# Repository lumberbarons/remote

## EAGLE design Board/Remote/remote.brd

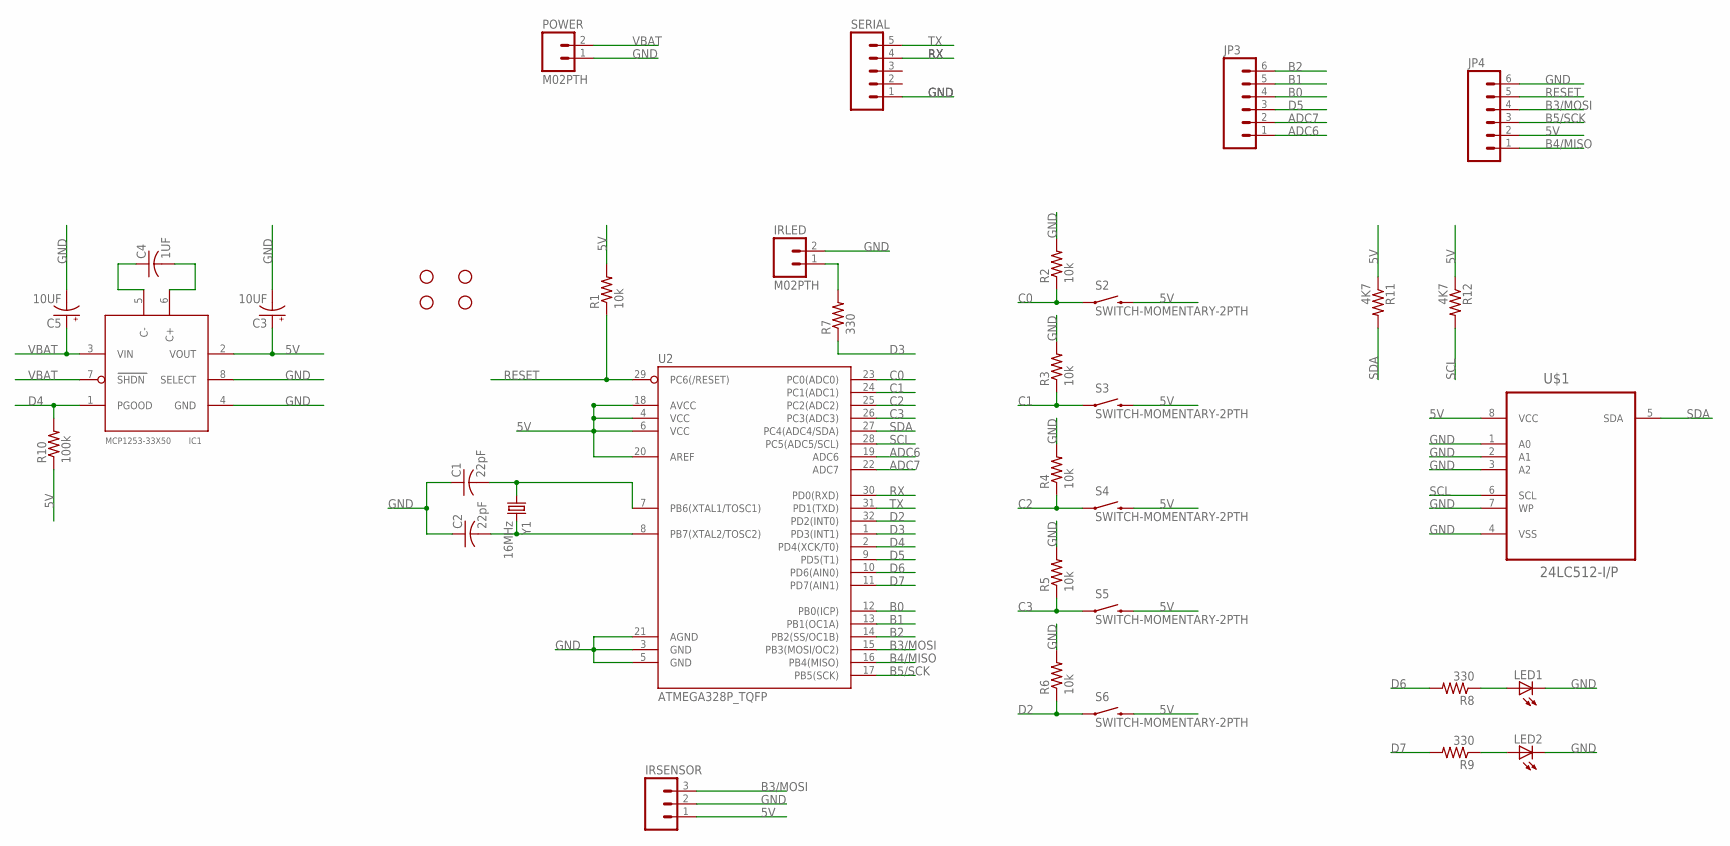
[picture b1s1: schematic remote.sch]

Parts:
C1, C2: 22pF; C0805
C3, C5: 10UF; A/3216-18W
C4: 1UF; C0805
IC1: MCP1253-33X50; MSOP8
IRLED: M02PTH; 1X02
IRSENSOR: M03PTH; 1X03
JP1, JP2, JP6, JP7: STAND-OFF
JP3, JP4: M06SIP; 1X06
LED1, LED2: LEDCHIPLED_0805; CHIPLED_0805
POWER: M02PTH; 1X02
R1, R2, R3, R4, R5, R6: 10k; R0805
R7, R8, R9: 330; R0805
R10: 100k; R0805
R11, R12: 4K7; R0805
S2, S3, S4, S5, S6: SWITCH-MOMENTARY-2PTH; TACTILE-PTH
SERIAL: M05PTH; 1X05
U2: ATMEGA328P_TQFP; TQFP32-08
U$1: 24LC512-I/P; DIP254P762X432-8
Y1: 16MHz; HC49US

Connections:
5V: C3.+, IC1.2 (VOUT), IRSENSOR.1, JP4.2, R1.2, R10.1, R11.1, R12.1, S2.3 (2), S3.3 (2), S4.3 (2), S5.3 (2), S6.3 (2), U2.4 (VCC), U2.6 (VCC), U2.18 (AVCC), U2.20 (AREF), U$1.8 (VCC)
ADC6: JP3.1, U2.19 (ADC6)
ADC7: JP3.2, U2.22 (ADC7)
B0: JP3.4, U2.12 (PB0(ICP))
B1: JP3.5, U2.13 (PB1(OC1A))
B2: JP3.6, U2.14 (PB2(SS/OC1B))
B3/MOSI: IRSENSOR.3, JP4.4, U2.15 (PB3(MOSI/OC2))
B4/MISO: JP4.1, U2.16 (PB4(MISO))
B5/SCK: JP4.3, U2.17 (PB5(SCK))
C0: R2.1, S2.1, U2.23 (PC0(ADC0))
C1: R3.1, S3.1, U2.24 (PC1(ADC1))
C2: R4.1, S4.1, U2.25 (PC2(ADC2))
C3: R5.1, S5.1, U2.26 (PC3(ADC3))
D2: R6.1, S6.1, U2.32 (PD2(INT0))
D3: R7.1, U2.1 (PD3(INT1))
D4: IC1.1 (PGOOD), R10.2, U2.2 (PD4(XCK/T0))
D5: JP3.3, U2.9 (PD5(T1))
D6: R8.2, U2.10 (PD6(AIN0))
D7: R9.2, U2.11 (PD7(AIN1))
GND: C1.1, C2.1, C3.-, C5.-, IC1.4 (GND), IC1.8 (SELECT), IRLED.2, IRSENSOR.2, JP4.6, LED1.C, LED2.C, POWER.1, R2.2, R3.2, R4.2, R5.2, R6.2, SERIAL.1, U2.3 (GND), U2.5 (GND), U2.21 (AGND), U$1.1 (A0), U$1.2 (A1), U$1.3 (A2), U$1.4 (VSS), U$1.7 (WP)
unnamed: C1.2, U2.7 (PB6(XTAL1/TOSC1)), Y1.1
unnamed: C2.2, U2.8 (PB7(XTAL2/TOSC2)), Y1.2
unnamed: IRLED.1, R7.2
unnamed: LED1.A, R8.1
unnamed: LED2.A, R9.1
unnamed: C4.1, IC1.5 (C-)
unnamed: C4.2, IC1.6 (C+)
RESET: JP4.5, R1.1, U2.29 (PC6(/RESET))
RX: SERIAL.4, U2.30 (PD0(RXD))
SCL: R12.2, U2.28 (PC5(ADC5/SCL)), U$1.6 (SCL)
SDA: R11.2, U2.27 (PC4(ADC4/SDA)), U$1.5 (SDA)
TX: SERIAL.5, U2.31 (PD1(TXD))
VBAT: C5.+, IC1.3 (VIN), IC1.7 (SHDN), POWER.2

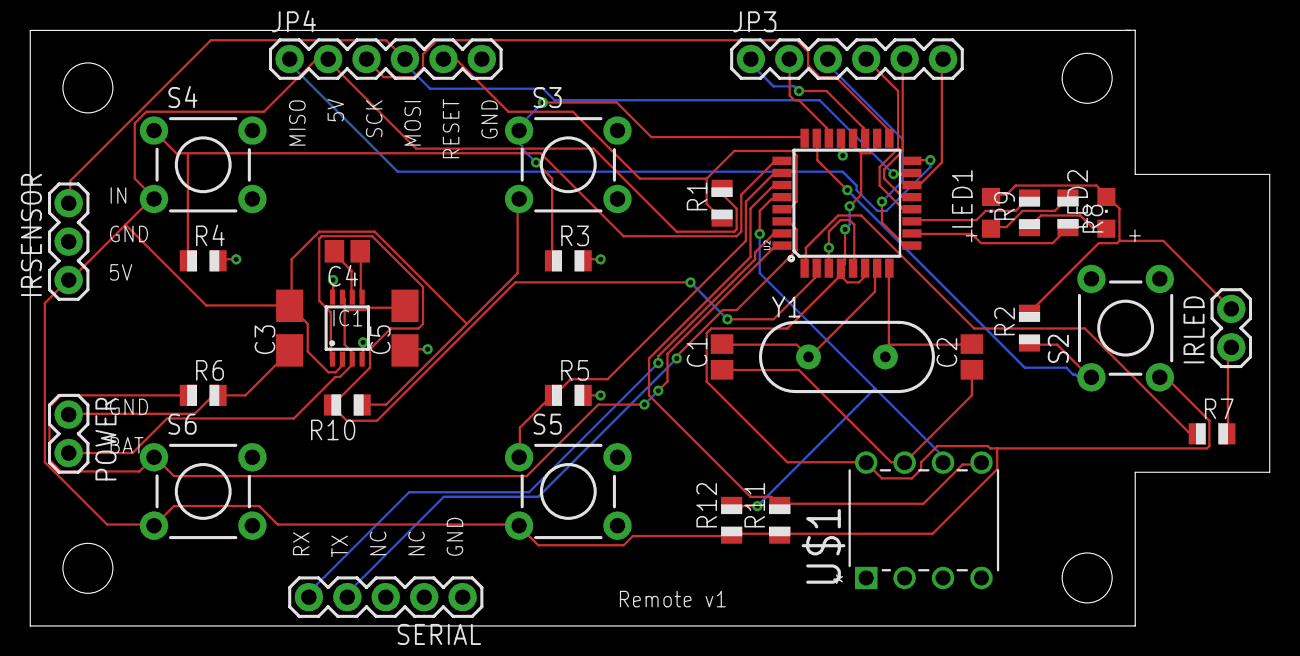
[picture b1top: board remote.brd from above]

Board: 2 copper layers, 81.9 x 39.4 mm, 38 parts (0 on the bottom side), 33 nets.

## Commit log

2015-03-01 Add shell of remote control PIC firmware.
2015-03-03 Make serial work, add an example command.
2015-03-21 Remove PIC project (using arduino instead) and commit enclosure model.
2015-03-21 Rename file - no need for version number.
2015-03-21 Remove file that was renamed.
2015-03-22 Commit first version of pcb eagle schematic and board.
2015-03-22 Latest enclosure design.
2015-04-17 Latest board layout - what was sent to oshpark.
2015-04-26 Latest enclosure, and first version of firmware.

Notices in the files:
parts and their libraries:
SparkFun-DigitalIC: Licensing: Creative Commons ShareAlike 4.0 International - https://creativecommons.org/licenses/by-sa/4.0
SparkFun-FreqCtrl: Licensing: CC v3.0 Share-Alike You are welcome to use this library for commercial purposes.
